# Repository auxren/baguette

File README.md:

# baguette

2hp euro module for passive banana<->euro conversion

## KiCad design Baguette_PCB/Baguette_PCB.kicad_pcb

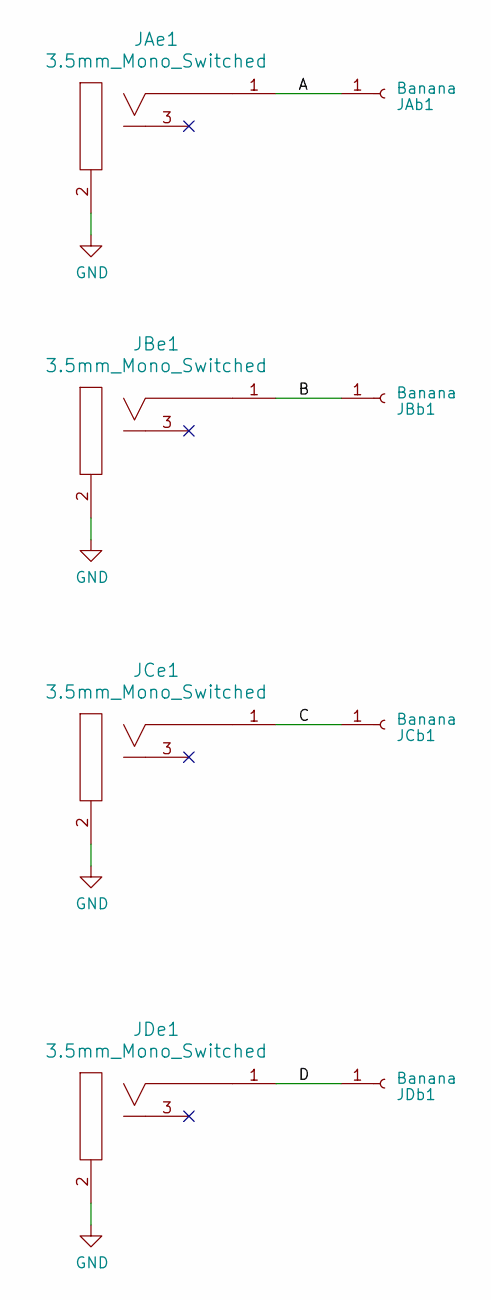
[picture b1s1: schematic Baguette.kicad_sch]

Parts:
JAb1: Banana; Johnson_108-09XX-001
JAe1: 3.5mm_Mono_Switched; EighthInch_PJ398SM; Part Number WQP-WQP518MA
JBb1: Banana; Johnson_108-09XX-001
JBe1: 3.5mm_Mono_Switched; EighthInch_PJ398SM; Part Number WQP-WQP518MA
JCb1: Banana; Johnson_108-09XX-001
JCe1: 3.5mm_Mono_Switched; EighthInch_PJ398SM; Part Number WQP-WQP518MA
JDb1: Banana; Johnson_108-09XX-001
JDe1: 3.5mm_Mono_Switched; EighthInch_PJ398SM; Part Number WQP-WQP518MA

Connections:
/A: JAb1.1, JAe1.1 (SIG)
/B: JBb1.1, JBe1.1 (SIG)
/C: JCb1.1, JCe1.1 (SIG)
/D: JDb1.1, JDe1.1 (SIG)
GND: JAe1.2 (SHEILD), JBe1.2 (SHEILD), JCe1.2 (SHEILD), JDe1.2 (SHEILD)

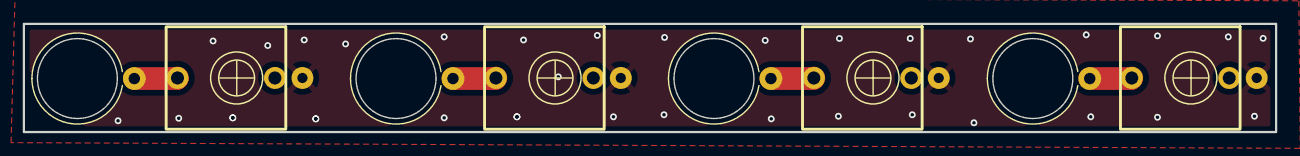
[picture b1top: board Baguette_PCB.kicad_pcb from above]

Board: 2 copper layers, 110.0 x 9.5 mm, 8 parts (0 on the bottom side), 5 nets.

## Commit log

2024-05-25 IntialCommit
2024-05-25 PanelCad
